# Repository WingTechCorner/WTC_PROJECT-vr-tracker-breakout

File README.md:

# Wing's Vive VR Tracker PCB Interface

Simple interface board to provide breakouts for the Vive VR Tracker.

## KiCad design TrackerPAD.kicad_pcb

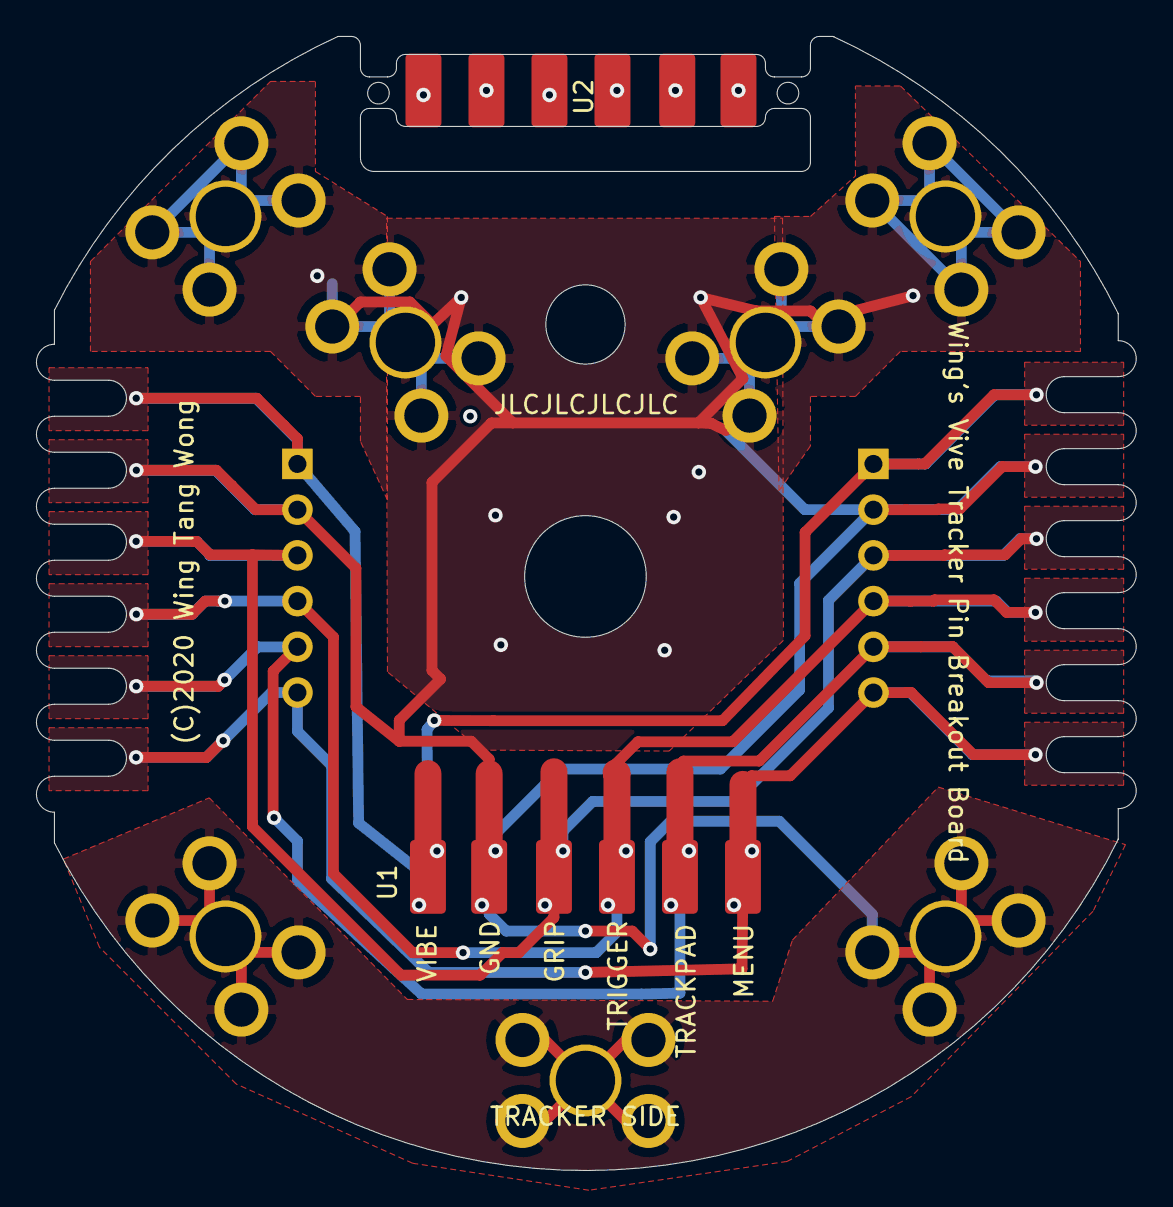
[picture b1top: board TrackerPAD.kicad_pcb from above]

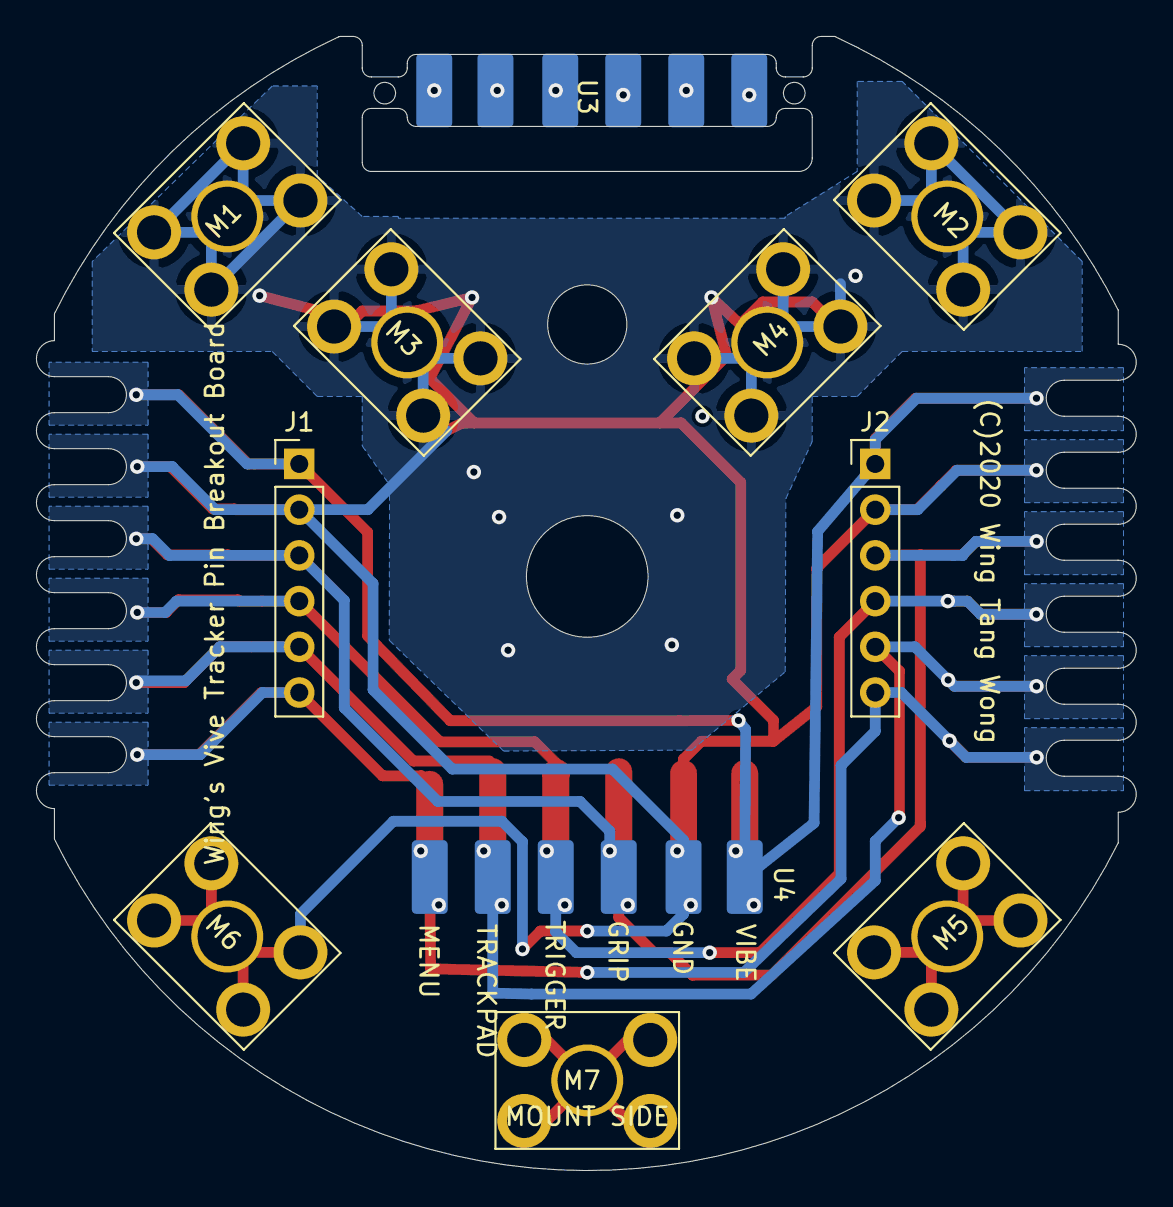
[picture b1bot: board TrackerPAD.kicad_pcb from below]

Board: 2 copper layers, 61.1 x 63.0 mm, 13 parts (11 on the bottom side), 12 nets.

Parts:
J1, J2: Conn_01x06; PinHeader_1x06_P2.54mm_Vertical
M1, M2, M3, M4, M5, M6, M7: M3MountLugHole; M3-Mount-Lug-Hole
U1: ViveTracker-holes; VRPadMinOutline
U2, U3, U4: ViveTracker; SteamVR 6-pin Pad

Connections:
GND: J1.2, J2.2, M1.1, M2.1, M3.1, M4.1, M5.1, M6.1, M7.1, U1.2, U4.2
GND_SPACER: U2.2, U3.2
GRIP: J1.3, J2.3, U1.3, U4.3
GRIP_SPACER: U2.3, U3.3
MENU: J1.6, J2.6, U1.6, U4.6
MENU_SPACER: U2.6, U3.6
TRACKPAD: J1.5, J2.5, U1.5, U4.5
TRACKPAD_SPACER: U2.5, U3.5
TRIGGER: J1.4, J2.4, U1.4, U4.4
TRIGGER_SPACER: U2.4, U3.4
VIBRATION-DIO: J1.1, J2.1, U1.1, U4.1
VIBRATION-DIO_SPACER: U2.1, U3.1

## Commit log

2020-12-17 Migrate files over
2020-12-17 Added M3 mount bracket positions. Moved some traces and vias. Added ground plane for other half of board.

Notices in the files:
TrackerPAD.kicad_pcb:
(C)2020 Wing Tang Wong
